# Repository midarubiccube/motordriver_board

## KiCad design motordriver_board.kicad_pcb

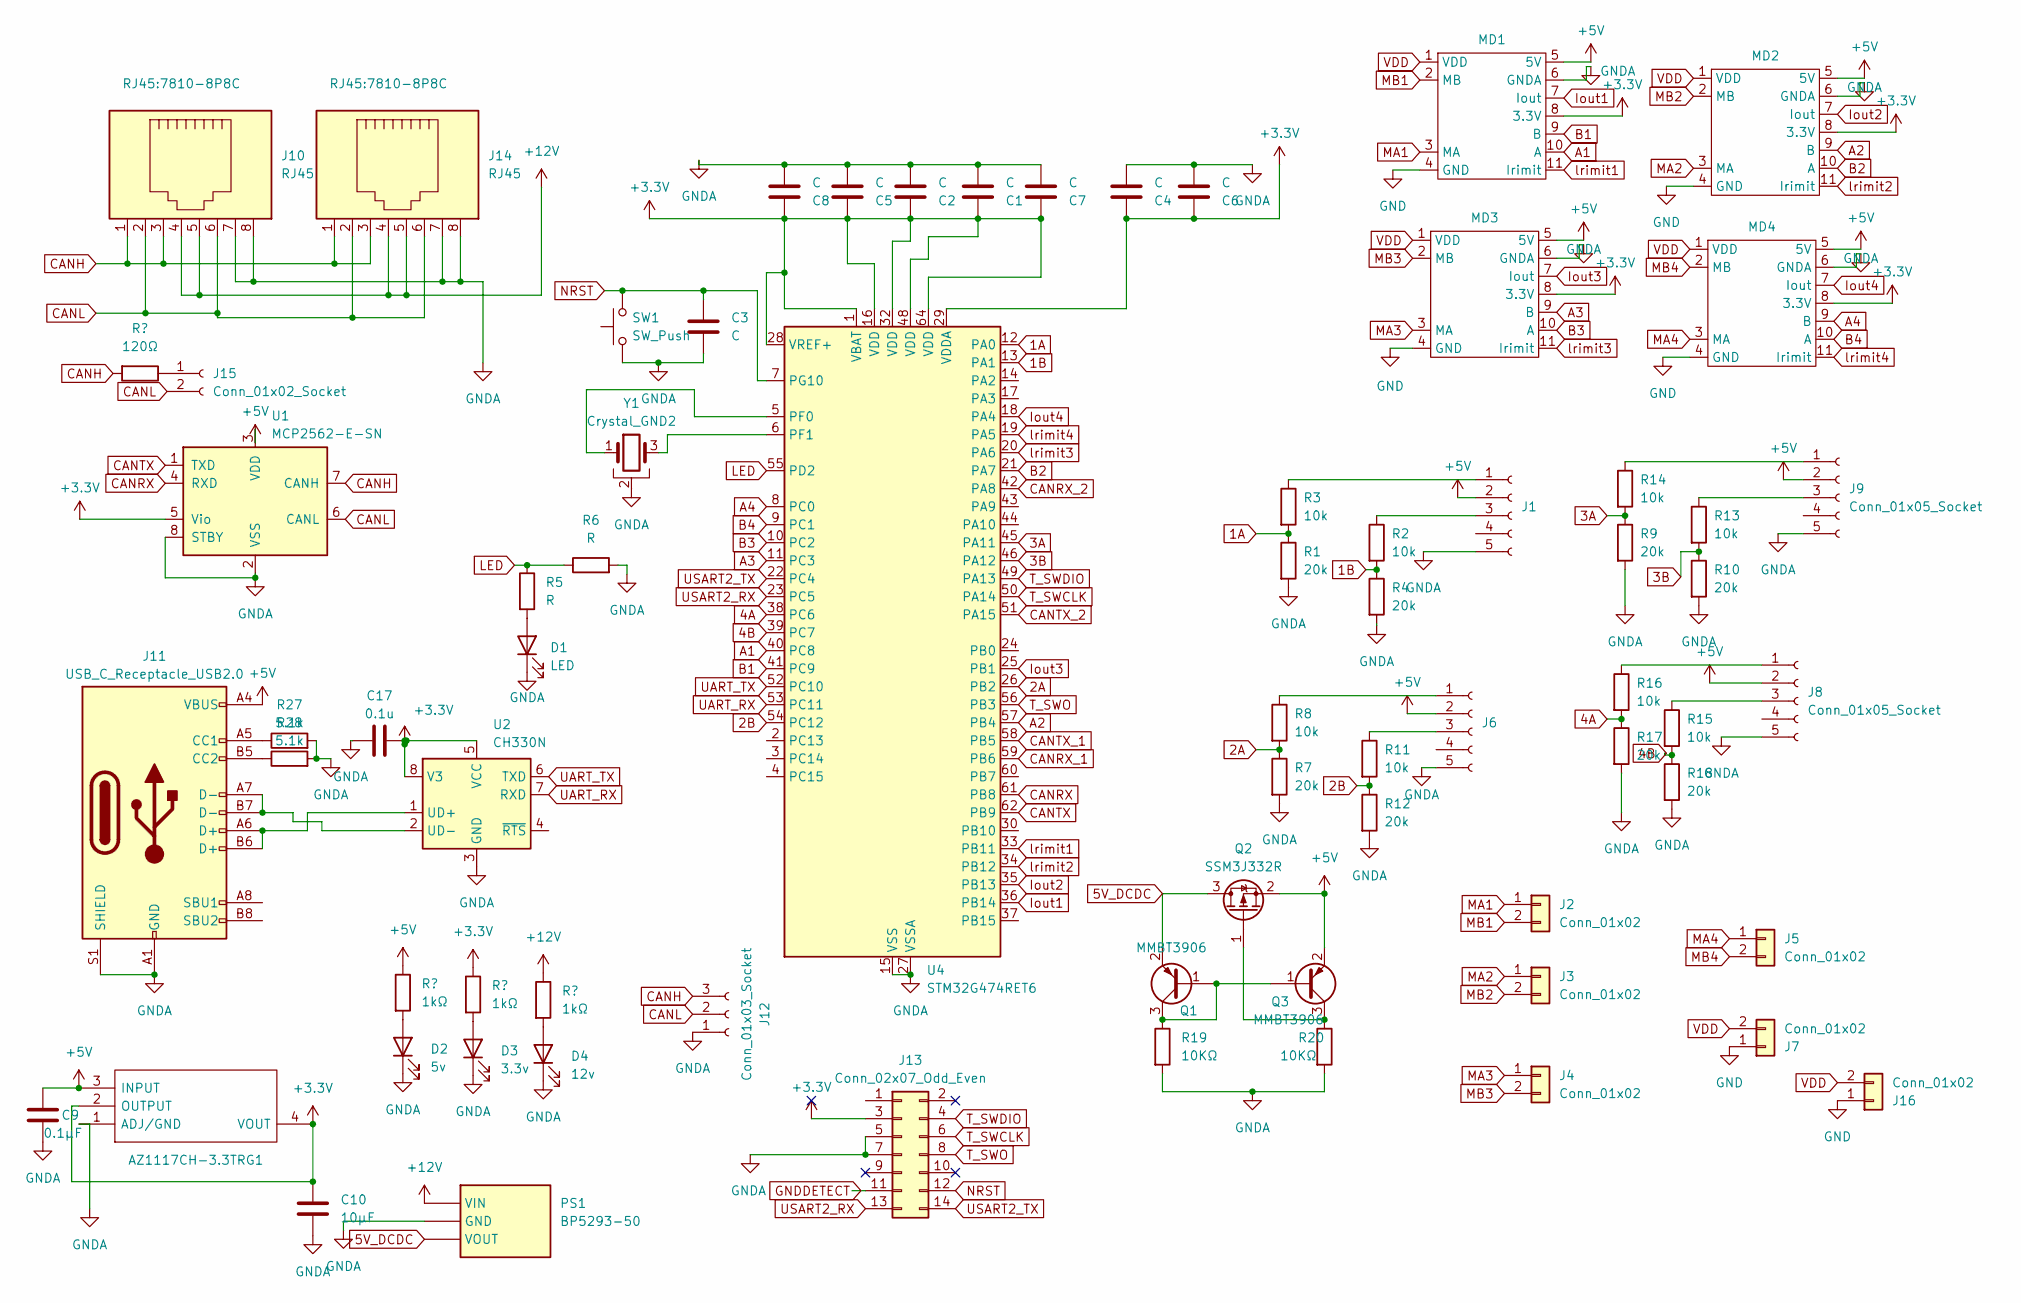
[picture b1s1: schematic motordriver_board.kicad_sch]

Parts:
C1, C2, C3, C4, C5, C6, C7, C8: C; C_0603_1608Metric_Pad1.08x0.95mm_HandSolder
C9: 0.1μF; C_0603_1608Metric_Pad1.08x0.95mm_HandSolder
C10: 10µF; C_0805_2012Metric_Pad1.18x1.45mm_HandSolder
C17: 0.1u; C_0603_1608Metric_Pad1.08x0.95mm_HandSolder; LCSC C14663
D1: LED; LED_0603_1608Metric_Pad1.05x0.95mm_HandSolder
D2: 5v; LED_0603_1608Metric_Pad1.05x0.95mm_HandSolder
D3: 3.3v; LED_0603_1608Metric_Pad1.05x0.95mm_HandSolder
D4: 12v; LED_0603_1608Metric_Pad1.05x0.95mm_HandSolder
IC1: AZ1117CH-3.3TRG1; SOT230P700X180-4N; Manufacturer_Part_Number AZ1117CH-3.3TRG1
J1, J6, J8, J9: Conn_01x05_Socket; JST_XH_B5B-XH-A_1x05_P2.50mm_Vertical
J2, J3, J4, J5: Conn_01x02; AMASS_XT60PW-F_1x02_P7.20mm_Horizontal
J7, J16: Conn_01x02; AMASS_XT60PW-M_1x02_P7.20mm_Horizontal
J10, J14: RJ45; 7810-8P8C
J11: USB_C_Receptacle_USB2.0; USB_C_Receptacle_HCTL_HC-TYPE-C-16P-01A
J12: Conn_01x03_Socket; PinHeader_1x03_P2.54mm_Vertical
J13: Conn_02x07_Odd_Even; connector
J15: Conn_01x02_Socket; PinHeader_1x02_P2.54mm_Vertical
MD1, MD2, MD3, MD4: MD_vetical
PS1: BP5293-50; TO254P570X1700X1780-3P; Manufacturer_Part_Number BP5293-50
Q1, Q3: MMBT3906; SOT-23
Q2: SSM3J332R; SOT-23
R1, R4, R7, R9, R10, R12, R17, R18: 20k; R_0603_1608Metric_Pad0.98x0.95mm_HandSolder
R2, R3, R8, R11, R13, R14, R15, R16: 10k; R_0603_1608Metric_Pad0.98x0.95mm_HandSolder
R5, R6: R; R_0603_1608Metric_Pad0.98x0.95mm_HandSolder
R19, R20: 10KΩ; R_0805_2012Metric_Pad1.20x1.40mm_HandSolder
R23, R24, R25: 1kΩ; R_0805_2012Metric_Pad1.20x1.40mm_HandSolder
R26: 120Ω; R_0805_2012Metric_Pad1.20x1.40mm_HandSolder
R27, R28: 5.1k; R_0603_1608Metric_Pad0.98x0.95mm_HandSolder; LCSC C23186
SW1: SW_Push; SW_PUSH_6mm_H5mm
U1: MCP2562-E-SN; SOIC-8_3.9x4.9mm_P1.27mm
U2: CH330N; SOIC-8_3.9x4.9mm_P1.27mm
U4: STM32G474RET6; LQFP-64_10x10mm_P0.5mm
Y1: Crystal_GND2; Resonator_SMD_Murata_CSTxExxV-3Pin_3.0x1.1mm_HandSoldering

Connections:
1A: R1.1, R3.2, U4.12 (PA0)
1B: R2.2, R4.1, U4.13 (PA1)
2A: R7.1, R8.2, U4.26 (PB2)
2B: R11.2, R12.1, U4.54 (PC12)
3A: R9.1, R14.2, U4.45 (PA11)
3B: R10.1, R13.2, U4.46 (PA12)
4A: R16.2, R17.1, U4.38 (PC6)
4B: R15.2, R18.1, U4.39 (PC7)
5V_DCDC: PS1.3 (VOUT), Q1.2 (E), Q2.3 (D)
+3.3V: C1.1, C2.1, C4.1, C5.1, C6.1, C7.1, C8.1, C10.1, IC1.2 (OUTPUT), IC1.4 (VOUT), J13.3, MD1.8 (3.3V), MD2.8 (3.3V), MD3.8 (3.3V), MD4.8 (3.3V), R24.1, U1.5 (Vio), U2.5 (VCC), U2.8 (V3), U4.1 (VBAT), U4.16 (VDD), U4.28 (VREF+), U4.29 (VDDA), U4.32 (VDD), U4.48 (VDD), U4.64 (VDD); also elsewhere on the board
+5V: C9.1, IC1.3 (INPUT), J1.2, J6.2, J8.2, J9.2, J11.A4 (VBUS), J11.A9 (VBUS), J11.B4 (VBUS), J11.B9 (VBUS), MD1.5 (5V), MD2.5 (5V), MD3.5 (5V), MD4.5 (5V), Q2.2 (S), Q3.2 (E), R23.1, U1.3 (VDD)
+12V: J10.4, J10.5, J14.4, J14.5, PS1.1 (VIN), R25.1
A1: MD1.10 (A), U4.40 (PC8)
A2: MD2.9 (B), U4.57 (PB4)
A3: MD3.9 (B), U4.11 (PC3)
A4: MD4.9 (B), U4.8 (PC0)
B1: MD1.9 (B), U4.41 (PC9)
B2: MD2.10 (A), U4.21 (PA7)
B3: MD3.10 (A), U4.10 (PC2)
B4: MD4.10 (A), U4.9 (PC1)
CANH: J10.1, J10.3, J12.3, J14.1, J14.3, R26.2, U1.7 (CANH)
CANL: J10.2, J10.6, J12.2, J14.2, J14.6, J15.2, U1.6 (CANL)
CANRX: U1.4 (RXD), U4.61 (PB8)
CANRX_1: U4.59 (PB6)
CANRX_2: U4.42 (PA8)
CANTX: U1.1 (TXD), U4.62 (PB9)
CANTX_1: U4.58 (PB5)
CANTX_2: U4.51 (PA15)
GND: J7.1, J16.1, MD1.4 (GND), MD2.4 (GND), MD3.4 (GND), MD4.4 (GND)
GNDA: C1.2, C2.2, C3.2, C4.2, C5.2, C6.2, C7.2, C8.2, C9.2, C10.2, D1.1 (K), D2.1 (K), D3.1 (K), D4.1 (K), IC1.1 (ADJ/GND), J1.5, J6.5, J8.5, J9.5, J10.7, J10.8, J11.A1 (GND), J11.A12 (GND), J11.B1 (GND), J11.B12 (GND), J11.S1 (SHIELD), J12.1, J13.5, J13.7, J14.7, J14.8, MD1.6 (GNDA), MD2.6 (GNDA), MD3.6 (GNDA), MD4.6 (GNDA), PS1.2 (GND), R1.2, R4.2, R6.2, R7.2, R9.2, R10.2, R12.2, R17.2, R18.2, R19.2, R20.2, SW1.1, U1.2 (VSS), U1.8 (STBY), U2.3 (GND), U4.15 (VSS), U4.27 (VSSA), U4.31 (VSS), U4.47 (VSS), U4.63 (VSS), Y1.2; also elsewhere on the board
GNDDETECT: J13.11
Iout1: MD1.7 (Iout), U4.36 (PB14)
Iout2: MD2.7 (Iout), U4.35 (PB13)
Iout3: MD3.7 (Iout), U4.25 (PB1)
Iout4: MD4.7 (Iout), U4.18 (PA4)
LED: R5.1, R6.1, U4.55 (PD2)
MA1: J2.1, MD1.3 (MA)
MA2: J3.1, MD2.3 (MA)
MA3: J4.1, MD3.3 (MA)
MA4: J5.1, MD4.3 (MA)
MB1: J2.2, MD1.2 (MB)
MB2: J3.2, MD2.2 (MB)
MB3: J4.2, MD3.2 (MB)
MB4: J5.2, MD4.2 (MB)
NRST: C3.1, J13.12, SW1.2, U4.7 (PG10)
unnamed: D1.2 (A), R5.2
unnamed: D2.2 (A), R23.2
unnamed: D3.2 (A), R24.2
unnamed: D4.2 (A), R25.2
unnamed: J1.1, R3.1
unnamed: J1.3, R2.1
unnamed: J6.1, R8.1
unnamed: J6.3, R11.1
unnamed: J8.1, R16.1
unnamed: J8.3, R15.1
unnamed: J9.1, R14.1
unnamed: J9.3, R13.1
unnamed 57: J11.A5 (CC1); also elsewhere on the board
unnamed 58: J11.B5 (CC2); also elsewhere on the board
unnamed: J15.1, R26.1
unnamed: Q1.1 (B), Q1.3 (C), Q3.1 (B), R19.1
unnamed: Q2.1 (G), Q3.3 (C), R20.1
unnamed: J11.A6 (D+), J11.B6 (D+), U2.1 (UD+)
unnamed: J11.A7 (D-), J11.B7 (D-), U2.2 (UD-)
unnamed: U4.5 (PF0), Y1.1
unnamed: U4.6 (PF1), Y1.3
T_SWCLK: J13.6, U4.50 (PA14)
T_SWDIO: J13.4, U4.49 (PA13)
T_SWO: J13.8, U4.56 (PB3)
UART_RX: U2.7 (RXD), U4.53 (PC11)
UART_TX: U2.6 (TXD), U4.52 (PC10)
USART2_RX: J13.13, U4.23 (PC5)
USART2_TX: J13.14, U4.22 (PC4)
VDD: J7.2, J16.2, MD1.1 (VDD), MD2.1 (VDD), MD3.1 (VDD), MD4.1 (VDD)
lrimit1: MD1.11 (Irimit), U4.33 (PB11)
lrimit2: MD2.11 (Irimit), U4.34 (PB12)
lrimit3: MD3.11 (Irimit), U4.20 (PA6)
lrimit4: MD4.11 (Irimit), U4.19 (PA5)

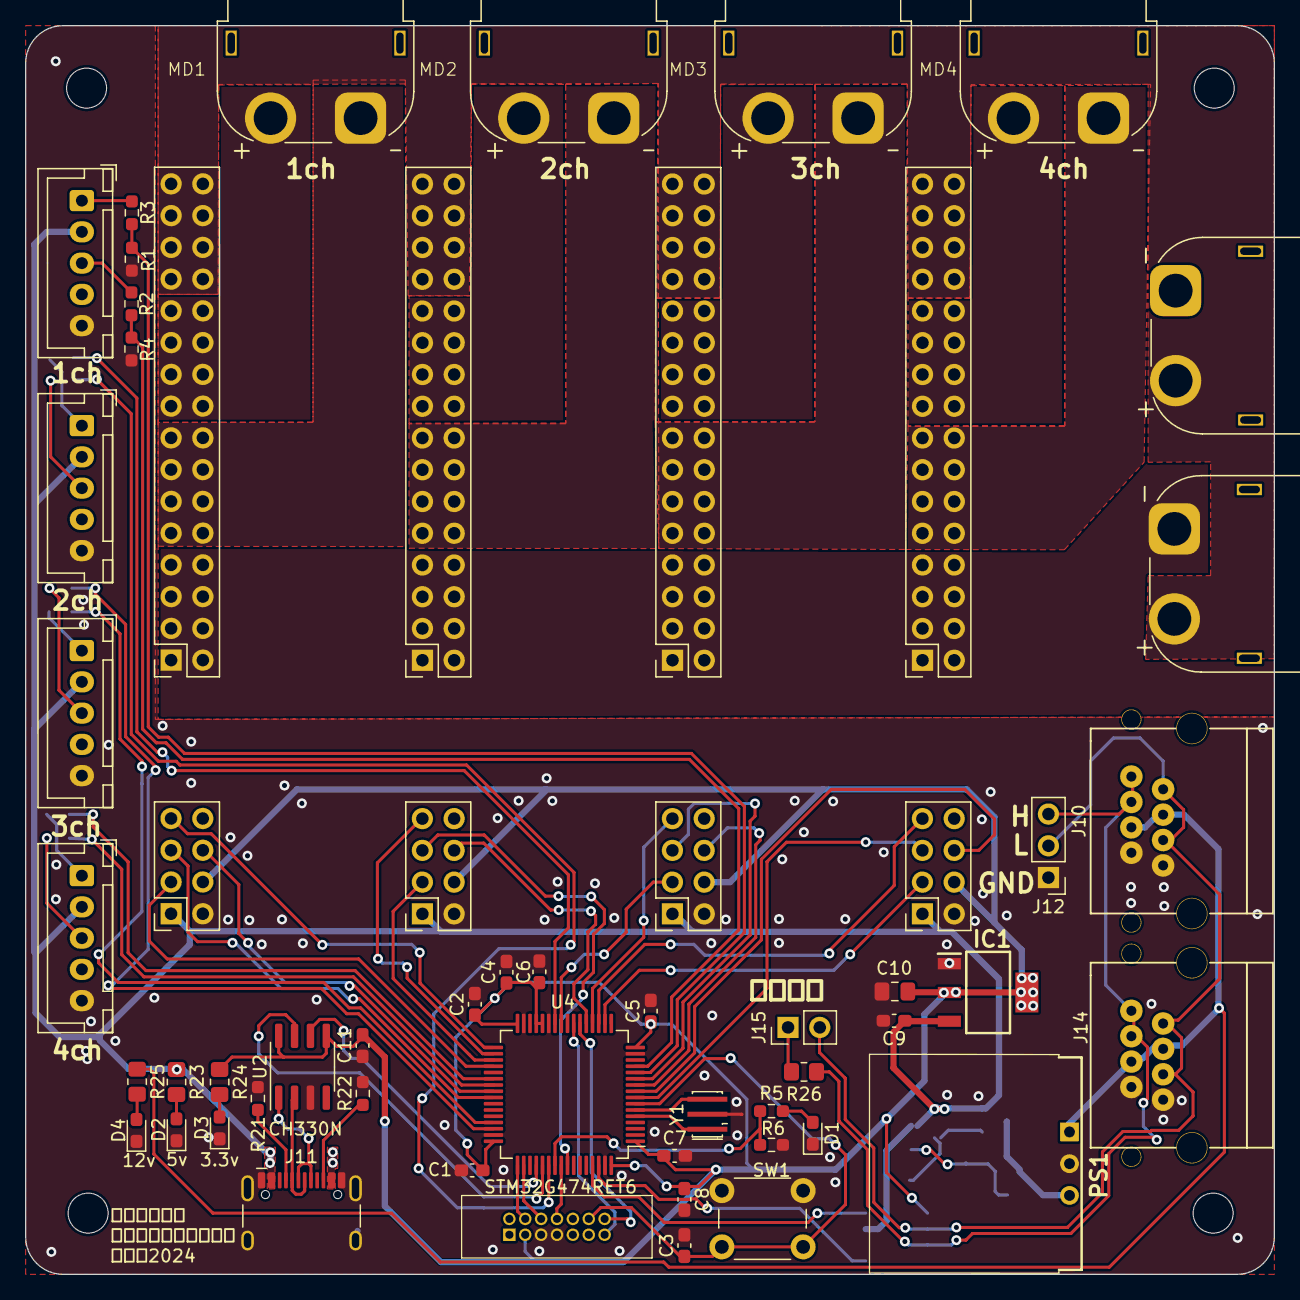
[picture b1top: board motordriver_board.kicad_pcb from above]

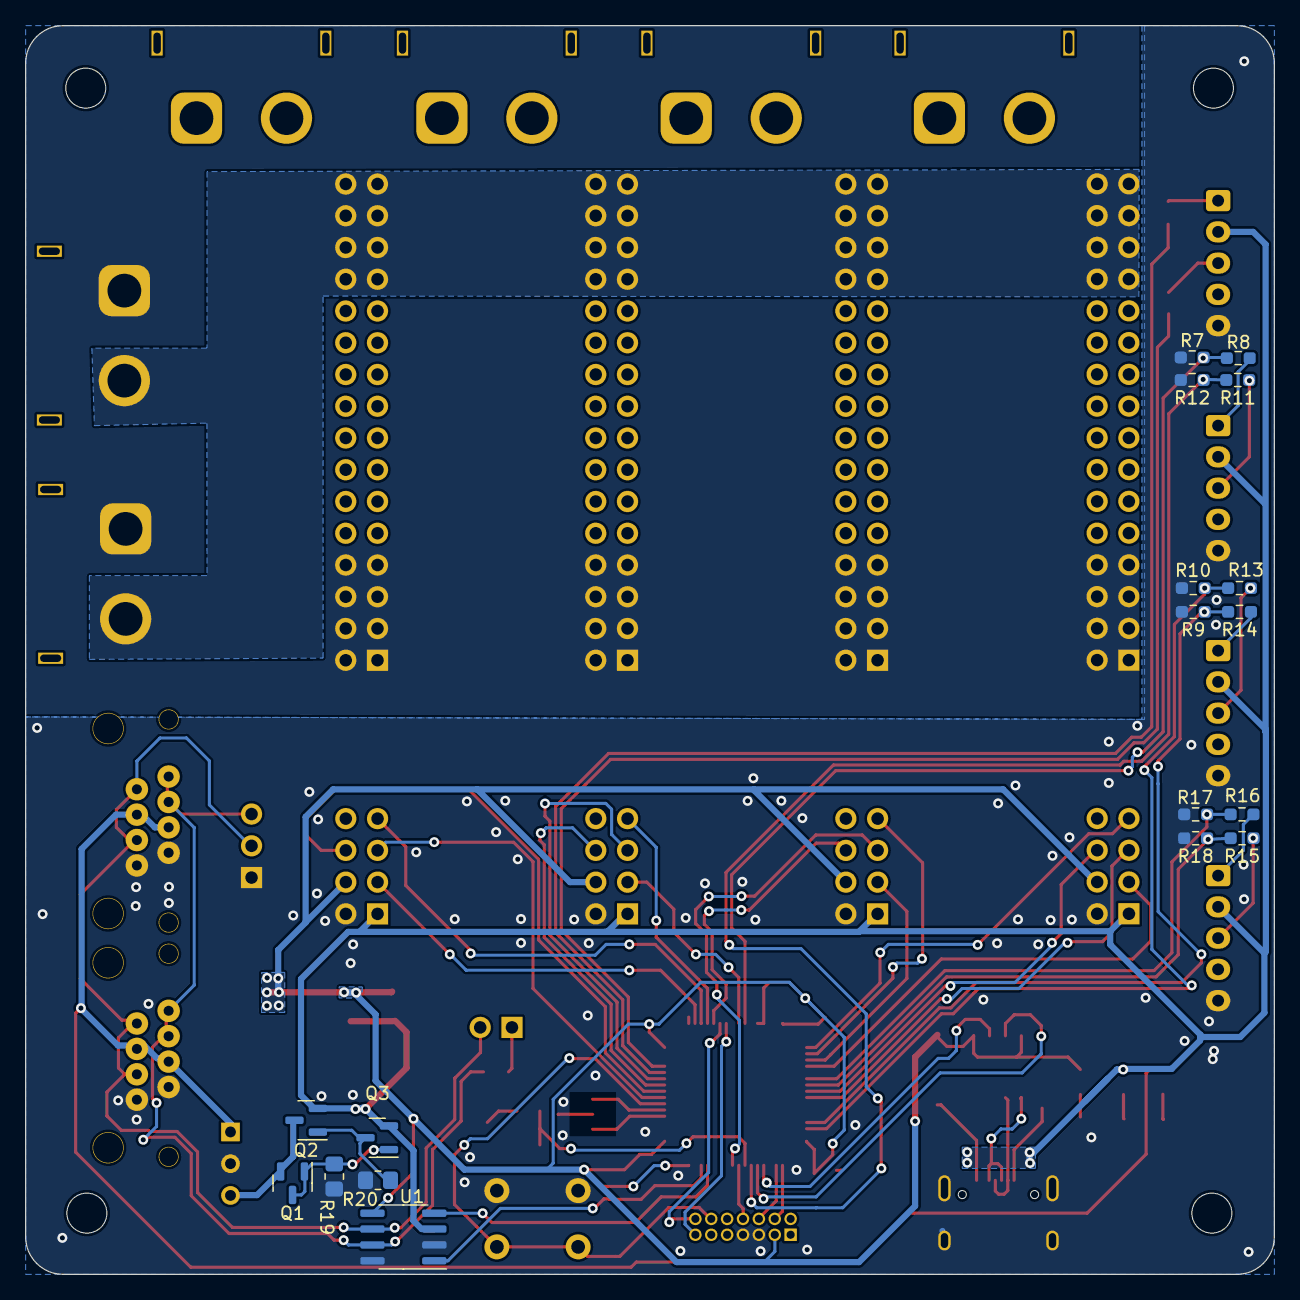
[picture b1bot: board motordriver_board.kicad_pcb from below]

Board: 2 copper layers, 99.9 x 99.9 mm, 71 parts (18 on the bottom side), 73 nets.

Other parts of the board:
C11: 0.1u; C_0603_1608Metric_Pad1.08x0.95mm_HandSolder
R21, R22: 5.1k; R_0603_1608Metric_Pad0.98x0.95mm_HandSolder

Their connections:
+3.3V: C11.2; also elsewhere on the board
GNDA: C11.1, R21.2, R22.2; also elsewhere on the board
unnamed 57: R21.1; also elsewhere on the board
unnamed 58: R22.1; also elsewhere on the board

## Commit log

2024-08-10 init commit
2024-09-26 並列にXT60追加
